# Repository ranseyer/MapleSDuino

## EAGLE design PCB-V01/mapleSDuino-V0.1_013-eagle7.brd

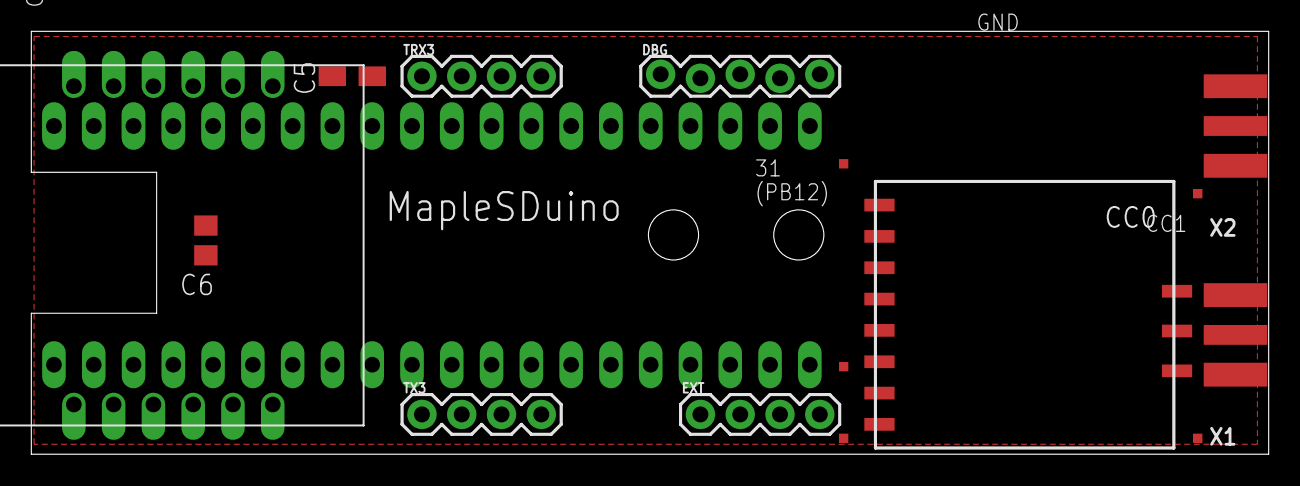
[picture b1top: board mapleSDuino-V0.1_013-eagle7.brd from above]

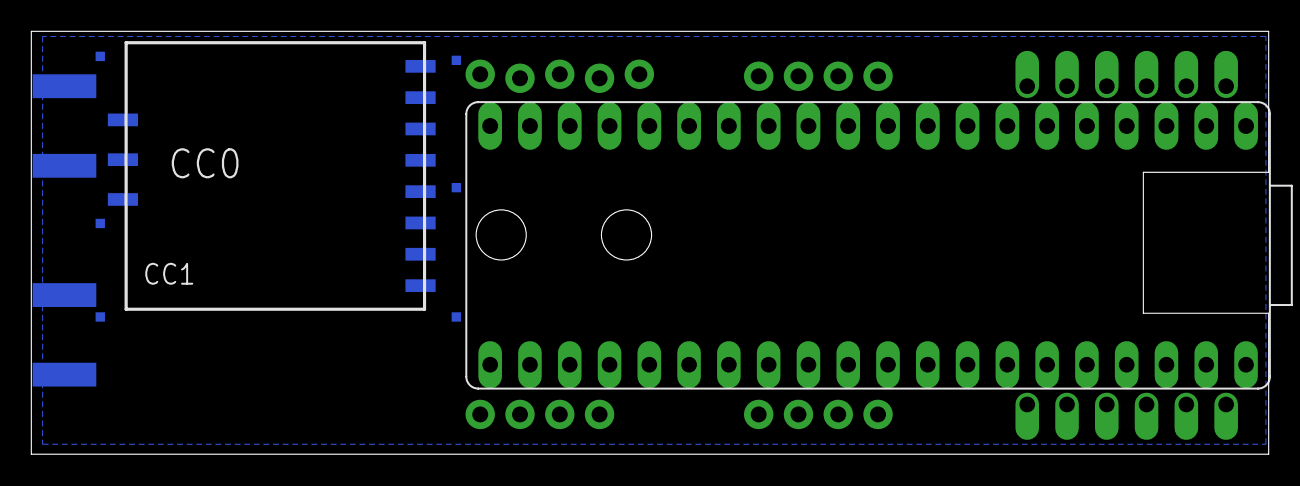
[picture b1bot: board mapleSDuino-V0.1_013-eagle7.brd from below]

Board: 2 copper layers, 79.0 x 27.0 mm, 23 parts (8 on the bottom side), 26 nets, no tracks yet.

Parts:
C5: 10uF; R/2012-12W
C6: 22pF; C0805
CC0: CC1101; CC1101_MODULE1_SMD
CC1: CC1101_MODULE1SMD; CC1101_MODULE1_SMD
DBG: 1X05_LOCK
EXT: 1X04
IC2: LAN-USR-ES1; USR-ES1
TP1, TP2, TP3, TP4, TP5, TP6, TP7, TP8, TP9, TP10, TP11: TPTP06SQ; TP06SQ
TRX3: 1X04
TX3: 1X04
U$1: MAPLEMINI; 20-DIP
X1, X2: SMA_EDGELAUNCH

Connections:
+5V: DBG.1, U$1.21
ANT1: CC1.ANT, X2.P
ANT2: CC0.ANT, X1.P
CC_CS0: CC0.CSN, U$1.20
CC_CS1: CC1.CSN, U$1.35
CC_CS2: TX3.4, U$1.4
CC_IN_0: CC0.GDO2, U$1.33
CC_IN_1: CC1.GDO2, U$1.7
CC_IN_2: TX3.2, U$1.5
CC_OUT_0: CC0.GDO0, U$1.32
CC_OUT_1: CC1.GDO0, U$1.6
CC_OUT_2: TX3.3, U$1.36
GND: C5.-, C6.2, CC0.GND@0, CC0.GND@1, CC0.GND@2, CC1.GND@0, CC1.GND@1, CC1.GND@2, DBG.5, EXT.4, IC2.1, IC2.2, IC2.12, TP1.TP, TP2.TP, TP3.TP, TP4.TP, TP5.TP, TP6.TP, TP7.TP, TP8.TP, TP9.TP, TP10.TP, TP11.TP, TRX3.2, U$1.2, U$1.24, U$1.39, X1.GND@1, X1.GND@2, X1.GND@3, X1.GND@4, X2.GND@1, X2.GND@2, X2.GND@3, X2.GND@4
MISO1: IC2.7, U$1.27
MISO2: CC0.MISO, CC1.MISO, TX3.1, U$1.18
MOSI1: IC2.3, U$1.26
MOSI2: CC0.MOSI, CC1.MOSI, TRX3.3, U$1.17
RX1: DBG.4, U$1.14
RX2: EXT.3, U$1.30
SCK1: IC2.4, U$1.28
SCK2: CC0.SCLK, CC1.SCLK, TRX3.4, U$1.19
SS1: IC2.5, U$1.29
TX1: DBG.3, U$1.15
TX2: EXT.2, U$1.31
VCC: C5.+, C6.1, CC0.VCC, CC1.VCC, DBG.2, EXT.1, IC2.10, IC2.11, TRX3.1, U$1.1, U$1.40
WIZ_RST: IC2.8, U$1.16

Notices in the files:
parts and their libraries:
SparkFun-Connectors: Licensing: Creative Commons ShareAlike 4.0 International - https://creativecommons.org/licenses/by-sa/4.0
